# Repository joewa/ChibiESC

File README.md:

# ChibiESC

Free electric speed controller software using ChibiOS

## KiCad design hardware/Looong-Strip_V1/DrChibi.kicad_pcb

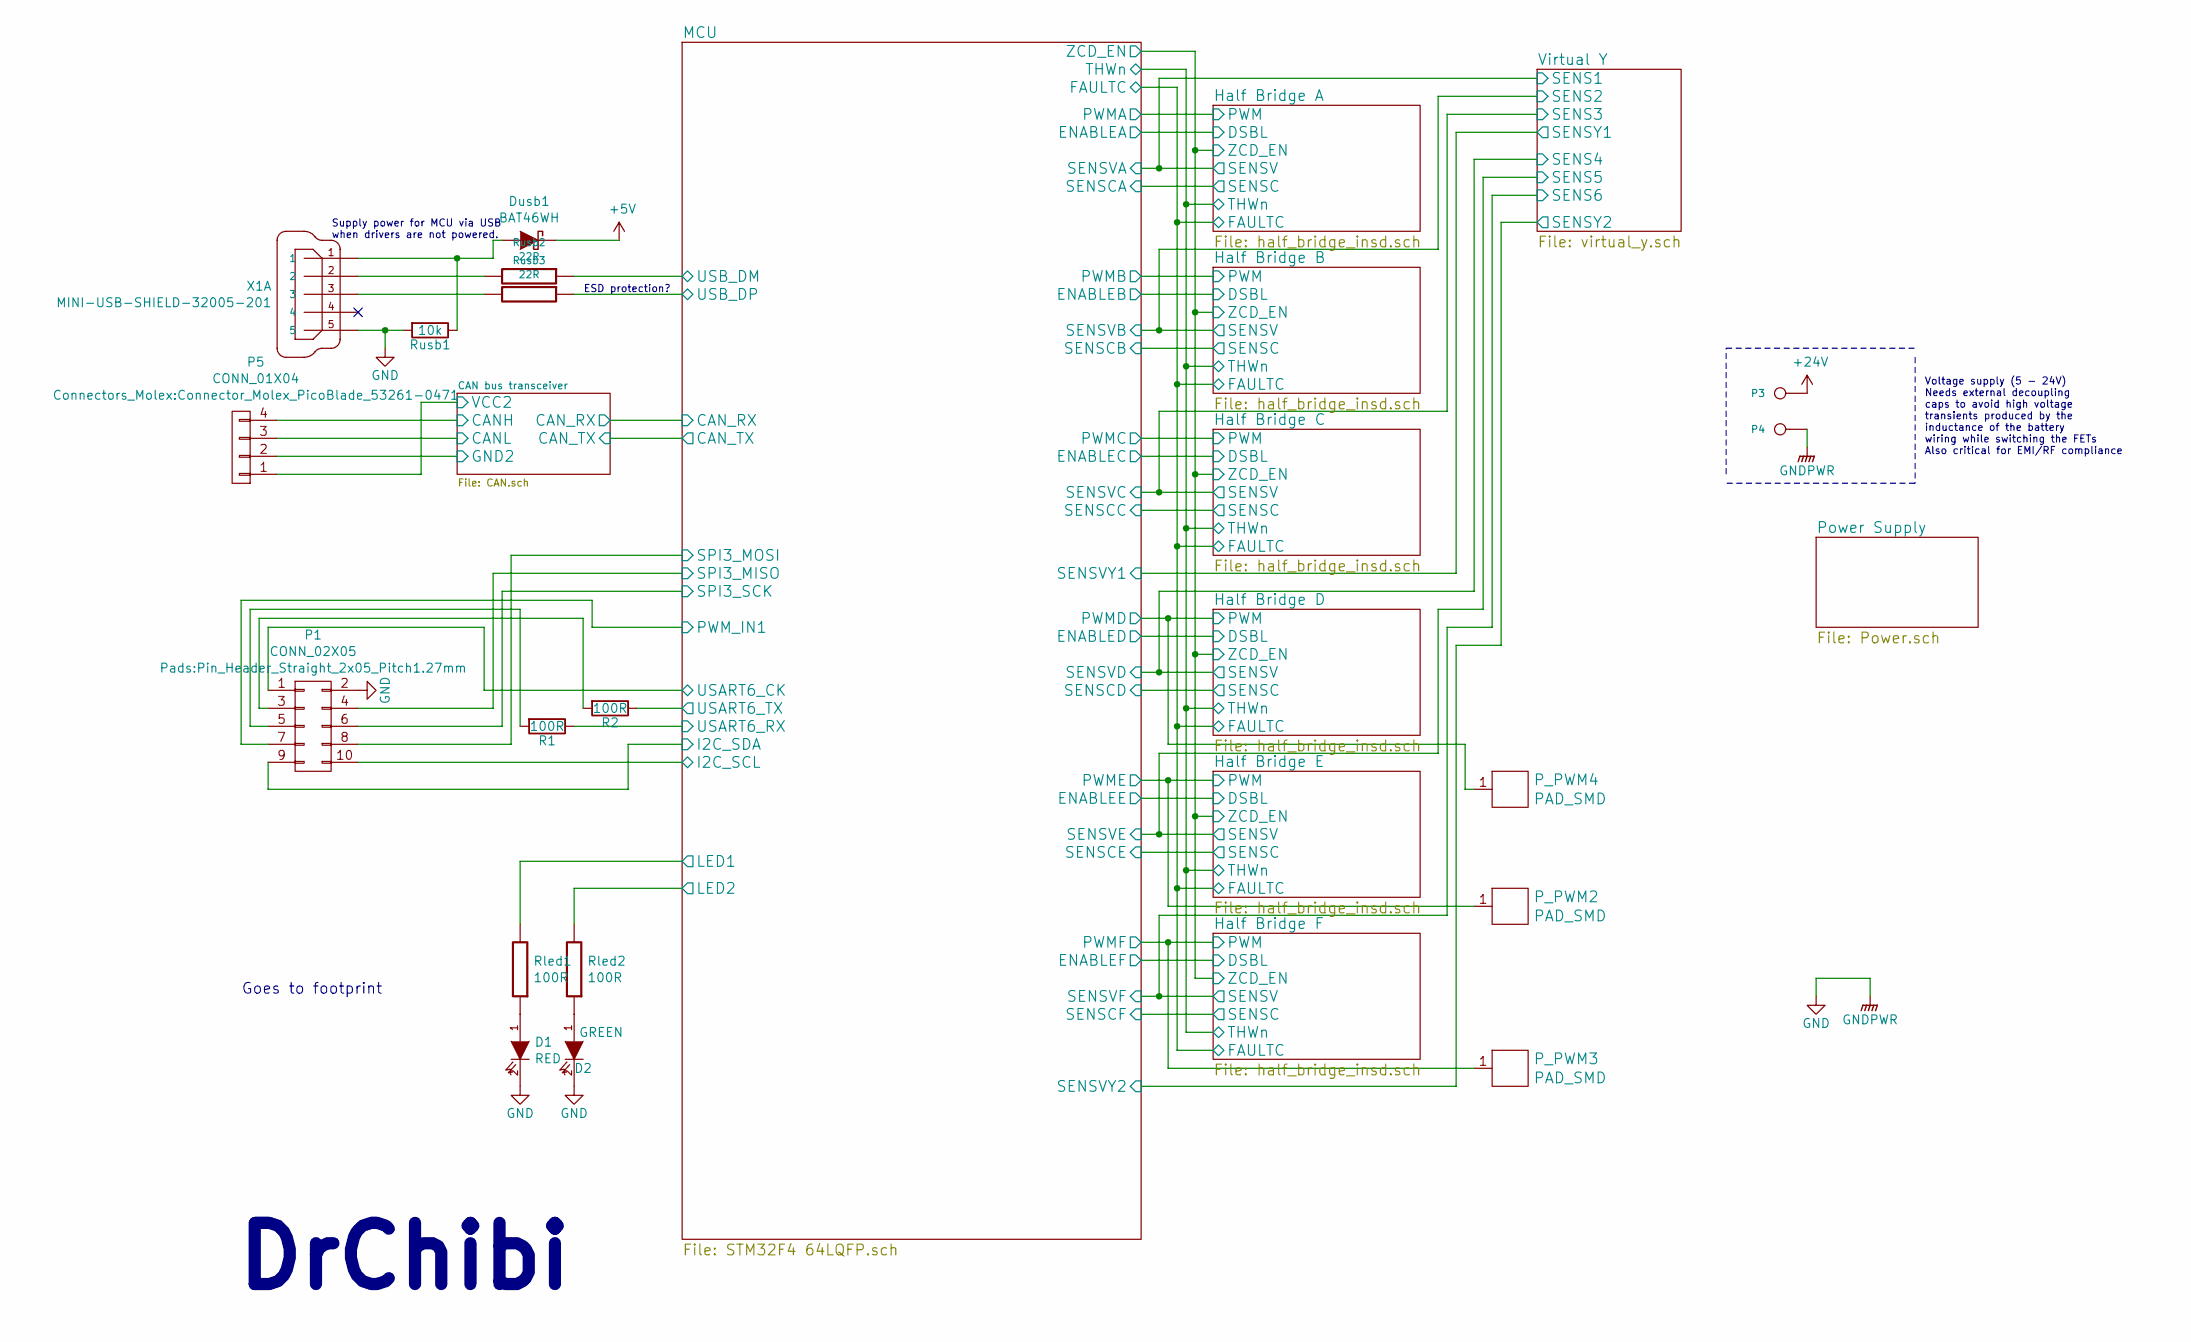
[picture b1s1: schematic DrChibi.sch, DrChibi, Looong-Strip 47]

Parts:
D1: RED; LED_0402
D2: GREEN; LED_0402
Dusb1: BAT46WH; SOD-123; Part Number BAT46WH
P1: CONN_02X05; Pin_Header_Straight_2x05_Pitch1.27mm
P3: IN+; 1PAD_3x6mm
P4: IN-; 1PAD_3.5x6mm
P5: CONN_01X04; Connector_Molex_PicoBlade_53261-0471; Part Number PicoBlade 53261-0471
P_PWM2, P_PWM3, P_PWM4: PAD_SMD; PAD_SMD_1x1
R1, R2: 100R; R_0603
Rled1, Rled2: 100R; R_0402
Rusb1: 10k; R_0402
Rusb2, Rusb3: 22R; R_0402
X1: MINI-USB-SHIELD-32005-201; mini_USB_gnd; Part Number CCMUSBB-32005-201

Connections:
+5V: Dusb1.1 (K); also elsewhere on the board
+24V: P3.1; also elsewhere on the board
/CAN bus transceiver/CANH: P5.4; also elsewhere on the board
/CAN bus transceiver/CANL: P5.3; also elsewhere on the board
/CAN bus transceiver/GND2: P5.2; also elsewhere on the board
/CAN bus transceiver/VCC2: P5.1; also elsewhere on the board
/Half Bridge D/PWM: P_PWM4.1; also elsewhere on the board
/Half Bridge E/PWM: P_PWM2.1; also elsewhere on the board
/Half Bridge F/PWM: P_PWM3.1; also elsewhere on the board
/MCU/I2C_SCL: P1.10; also elsewhere on the board
/MCU/I2C_SDA: P1.9; also elsewhere on the board
/MCU/LED1: Rled1.2; also elsewhere on the board
/MCU/LED2: Rled2.2; also elsewhere on the board
/MCU/PWM_IN1: P1.7; also elsewhere on the board
/MCU/SPI3_MISO: P1.4; also elsewhere on the board
/MCU/SPI3_MOSI: P1.8; also elsewhere on the board
/MCU/SPI3_SCK: P1.6; also elsewhere on the board
/MCU/USART6_CK: P1.1; also elsewhere on the board
/MCU/USART6_RX: R1.1; also elsewhere on the board
/MCU/USART6_TX: R2.1; also elsewhere on the board
/MCU/USB_DM: Rusb2.1; also elsewhere on the board
/MCU/USB_DP: Rusb3.1; also elsewhere on the board
GND: D1.2 (K), D2.2 (K), P1.2, P4.1, Rusb1.2, X1.5; also elsewhere on the board
unnamed: D1.1 (A), Rled1.1
unnamed: D2.1 (A), Rled2.1
unnamed: Dusb1.2 (A), Rusb1.1, X1.1
unnamed: P1.3, R2.2
unnamed: P1.5, R1.2
unnamed: Rusb2.2, X1.2
unnamed: Rusb3.2, X1.3

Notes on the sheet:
Supply power for MCU via USB when drivers are not powered.
ESD protection?
DrChibi
Voltage supply (5 - 24V) Needs external decoupling caps to avoid high voltage transients produced by the inductance of the battery wiring while switching the FETs Also critical for EMI/RF compliance
Goes to footprint

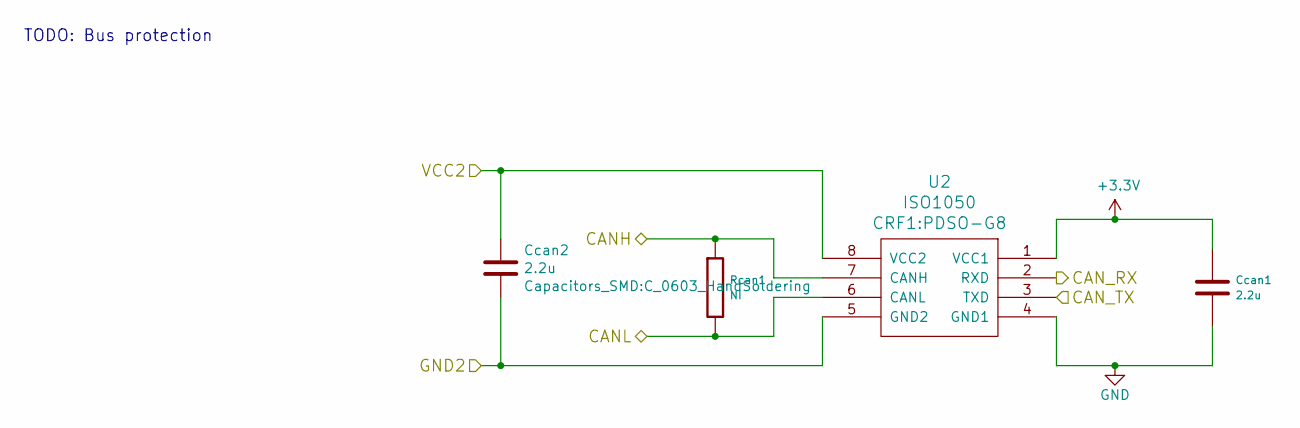
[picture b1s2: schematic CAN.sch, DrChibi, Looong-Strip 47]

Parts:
Ccan1: 2.2u; C_0603
Ccan2: 2.2u; C_0603_HandSoldering
Rcan1: NI; R_0603_HandSoldering
U2: ISO1050; PDSO-G8

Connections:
+3V3: Ccan1.1, U2.1 (VCC1); also elsewhere on the board
/CAN bus transceiver/CANH: Rcan1.1, U2.7 (CANH); also elsewhere on the board
/CAN bus transceiver/CANL: Rcan1.2, U2.6 (CANL); also elsewhere on the board
/CAN bus transceiver/CAN_RX: U2.2 (RXD); also elsewhere on the board
/CAN bus transceiver/CAN_TX: U2.3 (TXD); also elsewhere on the board
/CAN bus transceiver/GND2: Ccan2.2, U2.5 (GND2); also elsewhere on the board
/CAN bus transceiver/VCC2: Ccan2.1, U2.8 (VCC2); also elsewhere on the board
GND: Ccan1.2, U2.4 (GND1); also elsewhere on the board

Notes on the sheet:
TODO: Bus protection

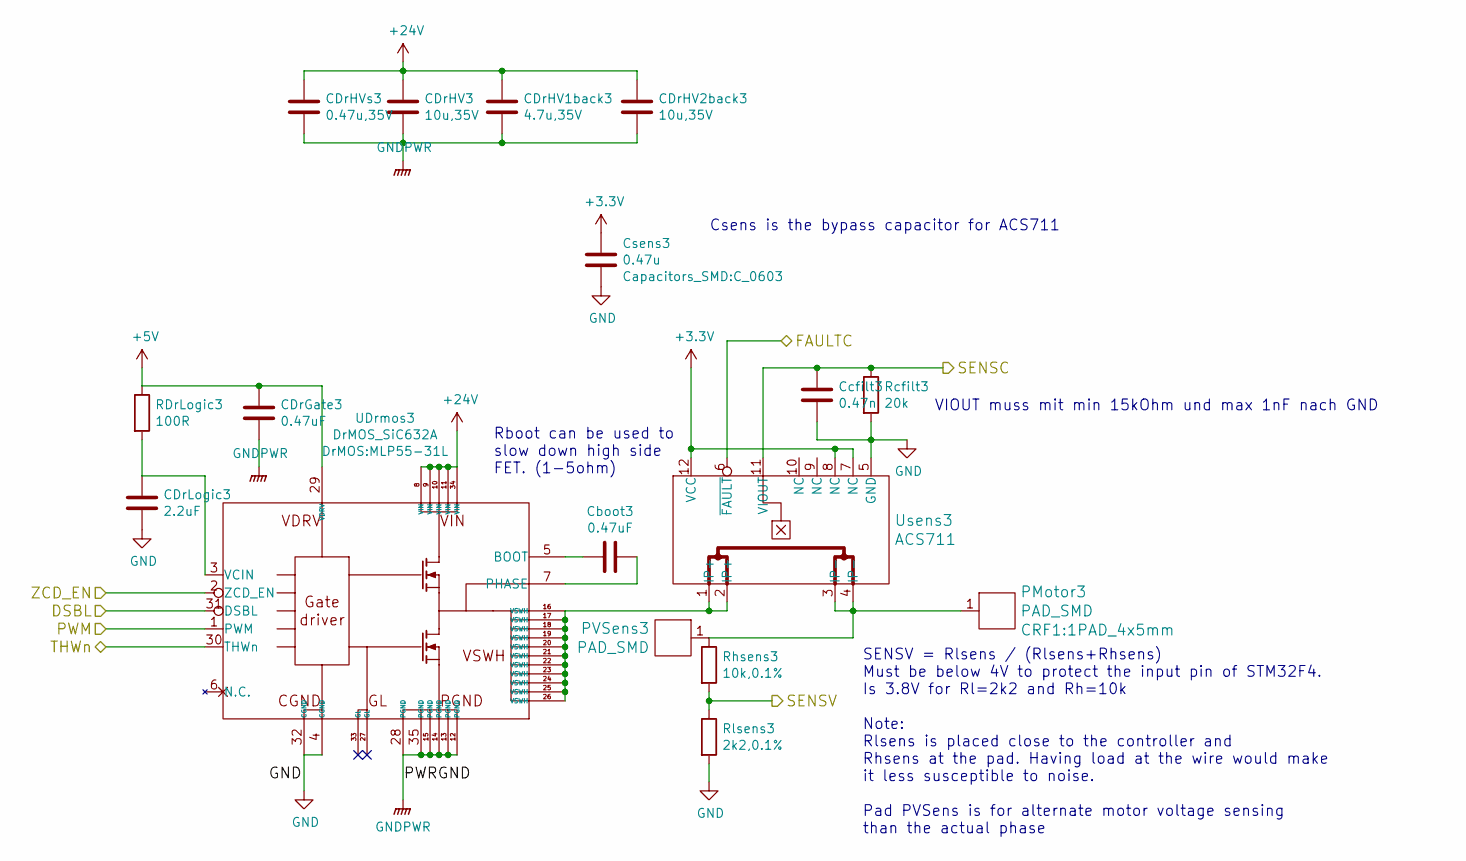
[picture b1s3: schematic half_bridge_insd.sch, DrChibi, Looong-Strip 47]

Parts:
CDrGate1: 0.47uF; C_0603_HandSoldering
CDrHV1: 10u,35V; C_1206
CDrHV1back1: 4.7u,35V; C_1206
CDrHV2back1: 10u,35V; C_1206_HandSoldering
CDrHVs1: 0.47u,35V; C_0603
CDrLogic1: 2.2uF; C_0603; Part Number C0603C225K8RACTU
Cboot1: 0.47uF; C_0603_HandSoldering
Ccfilt1: 0.47n; C_0402
Csens1: 0.47u; C_0603
PMotor1: PAD_SMD; 1PAD_4x5mm
PVSens1: PAD_SMD; PAD_SMD_1x1
RDrLogic1: 100R; R_0603
Rcfilt1: 20k; R_0402
Rhsens1: 10k,0.1%; C_0603_HandSoldering
Rlsens1: 2k2,0.1%; R_0402
UDrmos1: DrMOS_SiC632A; MLP55-31L; Part Number SiC632ACD-T1-GE3
Usens1: ACS711; QFN-12-1EX_3x3mm_Pitch0.5mm; Part Number ACS711KEXLT-31AB-T

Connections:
+3V3: Csens1.1, Usens1.7 (NC), Usens1.8 (NC), Usens1.12 (VCC); also elsewhere on the board
+5V: CDrGate1.1, RDrLogic1.1, UDrmos1.29 (VDRV); also elsewhere on the board
+24V: CDrHV1.1, CDrHV1back1.1, CDrHV2back1.1, CDrHVs1.1, UDrmos1.8 (VIN), UDrmos1.9 (VIN), UDrmos1.10 (VIN), UDrmos1.11 (VIN), UDrmos1.34 (VIN); also elsewhere on the board
/Half Bridge A/DSBL: UDrmos1.31 (DSBL); also elsewhere on the board
/Half Bridge A/FAULTC: Usens1.6 (~FAULT); also elsewhere on the board
/Half Bridge A/PWM: UDrmos1.1 (PWM); also elsewhere on the board
/Half Bridge A/SENSC: Ccfilt1.1, Rcfilt1.1, Usens1.11 (VIOUT); also elsewhere on the board
/Half Bridge A/THWn: UDrmos1.30 (THWn); also elsewhere on the board
/Half Bridge A/ZCD_EN: UDrmos1.2 (ZCD_EN); also elsewhere on the board
/Virtual Y/SENS1: Rhsens1.2, Rlsens1.1; also elsewhere on the board
GND: CDrGate1.2, CDrHV1.2, CDrHV1back1.2, CDrHV2back1.2, CDrHVs1.2, CDrLogic1.2, Ccfilt1.2, Csens1.2, Rcfilt1.2, Rlsens1.2, UDrmos1.4 (CGND), UDrmos1.12 (PGND), UDrmos1.13 (PGND), UDrmos1.14 (PGND), UDrmos1.15 (PGND), UDrmos1.28 (PGND), UDrmos1.32 (CGND), UDrmos1.35 (PGND), Usens1.5 (GND); also elsewhere on the board
unnamed: CDrLogic1.1, RDrLogic1.2, UDrmos1.3 (VCIN)
unnamed: Cboot1.1, UDrmos1.7 (PHASE)
unnamed: Cboot1.2, UDrmos1.5 (BOOT)
unnamed: PMotor1.1, PVSens1.1, Rhsens1.1, Usens1.3 (IP-), Usens1.4 (IP-)
unnamed: UDrmos1.16 (VSWH), UDrmos1.17 (VSWH), UDrmos1.18 (VSWH), UDrmos1.19 (VSWH), UDrmos1.20 (VSWH), UDrmos1.21 (VSWH), UDrmos1.22 (VSWH), UDrmos1.23 (VSWH), UDrmos1.24 (VSWH), UDrmos1.25 (VSWH), UDrmos1.26 (VSWH), Usens1.1 (IP+), Usens1.2 (IP+)

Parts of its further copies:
C20, C21, C22, C23: 0.47uF; C_0603_HandSoldering
CDrGate2, CDrGate3, CDrGate4, CDrGate5, CDrGate6: 0.47uF; C_0603_HandSoldering
CDrHV1back2, CDrHV1back3, CDrHV1back4, CDrHV1back5, CDrHV1back6: 4.7u,35V; C_1206
CDrHV2, CDrHV3, CDrHV4, CDrHV5, CDrHV6: 10u,35V; C_1206
CDrHV2back2, CDrHV2back3, CDrHV2back4, CDrHV2back5, CDrHV2back6: 10u,35V; C_1206_HandSoldering
CDrHVs2, CDrHVs3, CDrHVs4, CDrHVs5, CDrHVs6: 0.47u,35V; C_0603
CDrLogic2, CDrLogic3, CDrLogic4, CDrLogic5, CDrLogic6: 2.2uF; C_0603; Part Number C0603C225K8RACTU
Cboot2, Cboot3, Cboot4, Cboot5, Cboot6: 0.47uF; C_0603_HandSoldering
Ccfilt2, Ccfilt3, Ccfilt4, Ccfilt5, Ccfilt6: 0.47n; C_0402
Csens2, Csens3, Csens4, Csens5, Csens6: 0.47u; C_0603
PMotor2, PMotor3, PMotor4, PMotor5, PMotor6: PAD_SMD; 1PAD_4x5mm
PVSens2, PVSens3, PVSens4, PVSens5, PVSens6: PAD_SMD; PAD_SMD_1x1
RDrLogic2, RDrLogic3, RDrLogic4, RDrLogic5, RDrLogic6: 100R; R_0603
Rcfilt2, Rcfilt3, Rcfilt4, Rcfilt5, Rcfilt6: 20k; R_0402
Rhsens2, Rhsens3, Rhsens4, Rhsens5, Rhsens6: 10k,0.1%; C_0603_HandSoldering
Rlsens2, Rlsens3, Rlsens4, Rlsens5, Rlsens6: 2k2,0.1%; R_0402
UDrmos2, UDrmos3, UDrmos4, UDrmos5, UDrmos6: DrMOS_SiC632A; MLP55-31L; Part Number SiC632ACD-T1-GE3
Usens2, Usens3, Usens4, Usens5, Usens6: ACS711; QFN-12-1EX_3x3mm_Pitch0.5mm; Part Number ACS711KEXLT-31AB-T

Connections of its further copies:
+3V3: Csens2.1, Csens3.1, Csens4.1, Csens5.1, Csens6.1, Usens2.7 (NC), Usens2.8 (NC), Usens2.12 (VCC), Usens3.7 (NC), Usens3.8 (NC), Usens3.12 (VCC), Usens4.7 (NC), Usens4.8 (NC), Usens4.12 (VCC), Usens5.7 (NC), Usens5.8 (NC), Usens5.12 (VCC), Usens6.7 (NC), Usens6.8 (NC), Usens6.12 (VCC); also elsewhere on the board
+5V: CDrGate2.1, CDrGate3.1, CDrGate4.1, CDrGate5.1, CDrGate6.1, RDrLogic2.1, RDrLogic3.1, RDrLogic4.1, RDrLogic5.1, RDrLogic6.1, UDrmos2.29 (VDRV), UDrmos3.29 (VDRV), UDrmos4.29 (VDRV), UDrmos5.29 (VDRV), UDrmos6.29 (VDRV); also elsewhere on the board
+24V: CDrHV1back2.1, CDrHV1back3.1, CDrHV1back4.1, CDrHV1back5.1, CDrHV1back6.1, CDrHV2.1, CDrHV2back2.1, CDrHV2back3.1, CDrHV2back4.1, CDrHV2back5.1, CDrHV2back6.1, CDrHV3.1, CDrHV4.1, CDrHV5.1, CDrHV6.1, CDrHVs2.1, CDrHVs3.1, CDrHVs4.1, CDrHVs5.1, CDrHVs6.1, UDrmos2.8 (VIN), UDrmos2.9 (VIN), UDrmos2.10 (VIN), UDrmos2.11 (VIN), UDrmos2.34 (VIN), UDrmos3.8 (VIN), UDrmos3.9 (VIN), UDrmos3.10 (VIN), UDrmos3.11 (VIN), UDrmos3.34 (VIN), UDrmos4.8 (VIN), UDrmos4.9 (VIN), UDrmos4.10 (VIN), UDrmos4.11 (VIN), UDrmos4.34 (VIN), UDrmos5.8 (VIN), UDrmos5.9 (VIN), UDrmos5.10 (VIN), UDrmos5.11 (VIN), UDrmos5.34 (VIN), UDrmos6.8 (VIN), UDrmos6.9 (VIN), UDrmos6.10 (VIN), UDrmos6.11 (VIN), UDrmos6.34 (VIN); also elsewhere on the board
/Half Bridge A/FAULTC: Usens2.6 (~FAULT), Usens3.6 (~FAULT), Usens4.6 (~FAULT), Usens5.6 (~FAULT), Usens6.6 (~FAULT); also elsewhere on the board
/Half Bridge A/THWn: UDrmos2.30 (THWn), UDrmos3.30 (THWn), UDrmos4.30 (THWn), UDrmos5.30 (THWn), UDrmos6.30 (THWn); also elsewhere on the board
/Half Bridge A/ZCD_EN: UDrmos2.2 (ZCD_EN), UDrmos3.2 (ZCD_EN), UDrmos4.2 (ZCD_EN), UDrmos5.2 (ZCD_EN), UDrmos6.2 (ZCD_EN); also elsewhere on the board
/Half Bridge B/DSBL: UDrmos2.31 (DSBL); also elsewhere on the board
/Half Bridge B/PWM: UDrmos2.1 (PWM); also elsewhere on the board
/Half Bridge B/SENSC: Ccfilt2.1, Rcfilt2.1, Usens2.11 (VIOUT); also elsewhere on the board
/Half Bridge C/DSBL: UDrmos3.31 (DSBL); also elsewhere on the board
/Half Bridge C/PWM: UDrmos3.1 (PWM); also elsewhere on the board
/Half Bridge C/SENSC: Ccfilt3.1, Rcfilt3.1, Usens3.11 (VIOUT); also elsewhere on the board
/Half Bridge D/DSBL: UDrmos4.31 (DSBL); also elsewhere on the board
/Half Bridge D/PWM: UDrmos4.1 (PWM); also elsewhere on the board
/Half Bridge D/SENSC: Ccfilt4.1, Rcfilt4.1, Usens4.11 (VIOUT); also elsewhere on the board
/Half Bridge E/DSBL: UDrmos5.31 (DSBL); also elsewhere on the board
/Half Bridge E/PWM: UDrmos5.1 (PWM); also elsewhere on the board
/Half Bridge E/SENSC: Ccfilt5.1, Rcfilt5.1, Usens5.11 (VIOUT); also elsewhere on the board
/Half Bridge F/DSBL: UDrmos6.31 (DSBL); also elsewhere on the board
/Half Bridge F/PWM: UDrmos6.1 (PWM); also elsewhere on the board
/Half Bridge F/SENSC: Ccfilt6.1, Rcfilt6.1, Usens6.11 (VIOUT); also elsewhere on the board
/Virtual Y/SENS2: Rhsens2.2, Rlsens2.1; also elsewhere on the board
/Virtual Y/SENS3: Rhsens3.2, Rlsens3.1; also elsewhere on the board
/Virtual Y/SENS4: Rhsens4.2, Rlsens4.1; also elsewhere on the board
/Virtual Y/SENS5: Rhsens5.2, Rlsens5.1; also elsewhere on the board
/Virtual Y/SENS6: Rhsens6.2, Rlsens6.1; also elsewhere on the board
GND: CDrGate2.2, CDrGate3.2, CDrGate4.2, CDrGate5.2, CDrGate6.2, CDrHV1back2.2, CDrHV1back3.2, CDrHV1back4.2, CDrHV1back5.2, CDrHV1back6.2, CDrHV2.2, CDrHV2back2.2, CDrHV2back3.2, CDrHV2back4.2, CDrHV2back5.2, CDrHV2back6.2, CDrHV3.2, CDrHV4.2, CDrHV5.2, CDrHV6.2, CDrHVs2.2, CDrHVs3.2, CDrHVs4.2, CDrHVs5.2, CDrHVs6.2, CDrLogic2.2, CDrLogic3.2, CDrLogic4.2, CDrLogic5.2, CDrLogic6.2, Ccfilt2.2, Ccfilt3.2, Ccfilt4.2, Ccfilt5.2, Ccfilt6.2, Csens2.2, Csens3.2, Csens4.2, Csens5.2, Csens6.2, Rcfilt2.2, Rcfilt3.2, Rcfilt4.2, Rcfilt5.2, Rcfilt6.2, Rlsens2.2, Rlsens3.2, Rlsens4.2, Rlsens5.2, Rlsens6.2, UDrmos2.4 (CGND), UDrmos2.12 (PGND), UDrmos2.13 (PGND), UDrmos2.14 (PGND), UDrmos2.15 (PGND), UDrmos2.28 (PGND), UDrmos2.32 (CGND), UDrmos2.35 (PGND), UDrmos3.4 (CGND), UDrmos3.12 (PGND), UDrmos3.13 (PGND), UDrmos3.14 (PGND), UDrmos3.15 (PGND), UDrmos3.28 (PGND), UDrmos3.32 (CGND), UDrmos3.35 (PGND), UDrmos4.4 (CGND), UDrmos4.12 (PGND), UDrmos4.13 (PGND), UDrmos4.14 (PGND), UDrmos4.15 (PGND), UDrmos4.28 (PGND), UDrmos4.32 (CGND), UDrmos4.35 (PGND), UDrmos5.4 (CGND), UDrmos5.12 (PGND), UDrmos5.13 (PGND), UDrmos5.14 (PGND), UDrmos5.15 (PGND), UDrmos5.28 (PGND), UDrmos5.32 (CGND), UDrmos5.35 (PGND), UDrmos6.4 (CGND), UDrmos6.12 (PGND), UDrmos6.13 (PGND), UDrmos6.14 (PGND), UDrmos6.15 (PGND), UDrmos6.28 (PGND), UDrmos6.32 (CGND), UDrmos6.35 (PGND), Usens2.5 (GND), Usens3.5 (GND), Usens4.5 (GND), Usens5.5 (GND), Usens6.5 (GND); also elsewhere on the board
unnamed: CDrLogic2.1, RDrLogic2.2, UDrmos2.3 (VCIN)
unnamed: CDrLogic3.1, RDrLogic3.2, UDrmos3.3 (VCIN)
unnamed: CDrLogic4.1, RDrLogic4.2, UDrmos4.3 (VCIN)
unnamed: CDrLogic5.1, RDrLogic5.2, UDrmos5.3 (VCIN)
unnamed: CDrLogic6.1, RDrLogic6.2, UDrmos6.3 (VCIN)
unnamed: Cboot2.1, UDrmos2.7 (PHASE)
unnamed: Cboot2.2, UDrmos2.5 (BOOT)
unnamed: Cboot3.1, UDrmos3.7 (PHASE)
unnamed: Cboot3.2, UDrmos3.5 (BOOT)
unnamed: Cboot4.1, UDrmos4.7 (PHASE)
unnamed: Cboot4.2, UDrmos4.5 (BOOT)
unnamed: Cboot5.1, UDrmos5.7 (PHASE)
unnamed: Cboot5.2, UDrmos5.5 (BOOT)
unnamed: Cboot6.1, UDrmos6.7 (PHASE)
unnamed: Cboot6.2, UDrmos6.5 (BOOT)
unnamed: PMotor2.1, PVSens2.1, Rhsens2.1, Usens2.3 (IP-), Usens2.4 (IP-)
unnamed: PMotor3.1, PVSens3.1, Rhsens3.1, Usens3.3 (IP-), Usens3.4 (IP-)
unnamed: PMotor4.1, PVSens4.1, Rhsens4.1, Usens4.3 (IP-), Usens4.4 (IP-)
unnamed: PMotor5.1, PVSens5.1, Rhsens5.1, Usens5.3 (IP-), Usens5.4 (IP-)
unnamed: PMotor6.1, PVSens6.1, Rhsens6.1, Usens6.3 (IP-), Usens6.4 (IP-)
unnamed: UDrmos2.16 (VSWH), UDrmos2.17 (VSWH), UDrmos2.18 (VSWH), UDrmos2.19 (VSWH), UDrmos2.20 (VSWH), UDrmos2.21 (VSWH), UDrmos2.22 (VSWH), UDrmos2.23 (VSWH), UDrmos2.24 (VSWH), UDrmos2.25 (VSWH), UDrmos2.26 (VSWH), Usens2.1 (IP+), Usens2.2 (IP+)
unnamed: UDrmos3.16 (VSWH), UDrmos3.17 (VSWH), UDrmos3.18 (VSWH), UDrmos3.19 (VSWH), UDrmos3.20 (VSWH), UDrmos3.21 (VSWH), UDrmos3.22 (VSWH), UDrmos3.23 (VSWH), UDrmos3.24 (VSWH), UDrmos3.25 (VSWH), UDrmos3.26 (VSWH), Usens3.1 (IP+), Usens3.2 (IP+)
unnamed: UDrmos4.16 (VSWH), UDrmos4.17 (VSWH), UDrmos4.18 (VSWH), UDrmos4.19 (VSWH), UDrmos4.20 (VSWH), UDrmos4.21 (VSWH), UDrmos4.22 (VSWH), UDrmos4.23 (VSWH), UDrmos4.24 (VSWH), UDrmos4.25 (VSWH), UDrmos4.26 (VSWH), Usens4.1 (IP+), Usens4.2 (IP+)
unnamed: UDrmos5.16 (VSWH), UDrmos5.17 (VSWH), UDrmos5.18 (VSWH), UDrmos5.19 (VSWH), UDrmos5.20 (VSWH), UDrmos5.21 (VSWH), UDrmos5.22 (VSWH), UDrmos5.23 (VSWH), UDrmos5.24 (VSWH), UDrmos5.25 (VSWH), UDrmos5.26 (VSWH), Usens5.1 (IP+), Usens5.2 (IP+)
unnamed: UDrmos6.16 (VSWH), UDrmos6.17 (VSWH), UDrmos6.18 (VSWH), UDrmos6.19 (VSWH), UDrmos6.20 (VSWH), UDrmos6.21 (VSWH), UDrmos6.22 (VSWH), UDrmos6.23 (VSWH), UDrmos6.24 (VSWH), UDrmos6.25 (VSWH), UDrmos6.26 (VSWH), Usens6.1 (IP+), Usens6.2 (IP+)

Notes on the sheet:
VIOUT muss mit min 15kOhm und max 1nF nach GND
Rboot can be used to slow down high side FET. (1-5ohm)
SENSV = Rlsens / (Rlsens+Rhsens) Must be below 4V to protect the input pin of STM32F4. Is 3.8V for Rl=2k2 and Rh=10k Note: Rlsens is placed close to the controller and Rhsens at the pad. Having load at the wire would make it less susceptible to noise. Pad PVSens is for alternate motor voltage sensi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
Csens is the bypass capacitor for ACS711

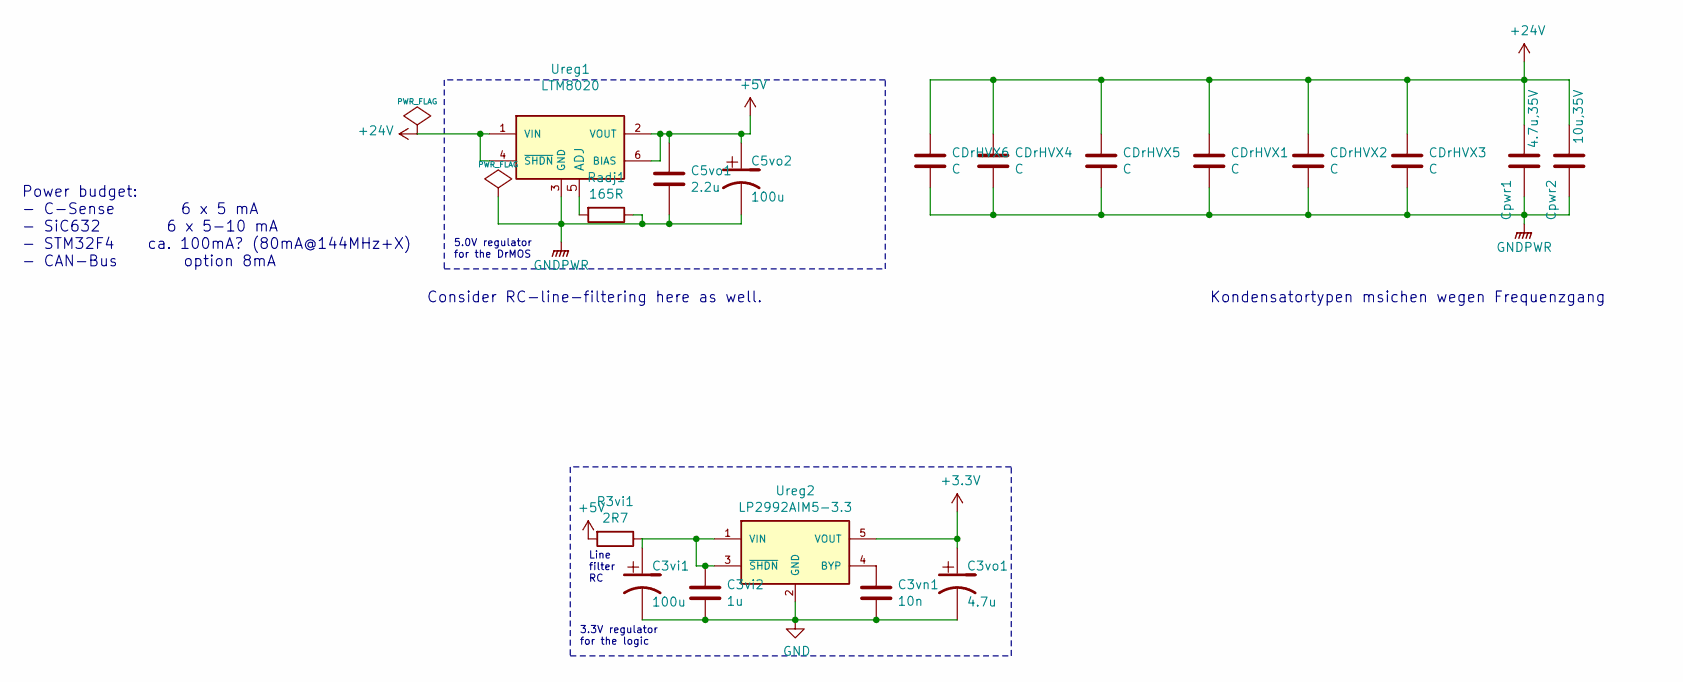
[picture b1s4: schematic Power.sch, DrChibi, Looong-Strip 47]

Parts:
C3vi1, C5vo2: 100u; C_0805
C3vi2: 1u; C_0603
C3vn1: 10n; C_0603
C3vo1: 4.7u; C_0805
C5vo1: 2.2u; C_0603
CDrHVX1, CDrHVX2, CDrHVX3, CDrHVX4, CDrHVX5, CDrHVX6: C; C_1206
Cpwr1: 4.7u,35V; C_0805
Cpwr2: 10u,35V; C_2220
R3vi1: 2R7; R_0805
Radj1: 165R; R_0402
Ureg1: LTM8020; Housings_LGA_21_6.25x6.25mm; Part Number LTM8020V
Ureg2: LP2992AIM5-3.3; SOT-23-5; Part Number LP2992AIM5-3.3/NOPB

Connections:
+3V3: C3vo1.1, Ureg2.5 (VOUT); also elsewhere on the board
+5V: C5vo1.1, C5vo2.1, R3vi1.2, Ureg1.2 (VOUT), Ureg1.6 (BIAS); also elsewhere on the board
+24V: CDrHVX1.1, CDrHVX2.1, CDrHVX3.1, CDrHVX4.1, CDrHVX5.1, CDrHVX6.1, Cpwr1.2, Cpwr2.2, Ureg1.1 (VIN), Ureg1.4 (~SHDN~); also elsewhere on the board
GND: C3vi1.2, C3vi2.2, C3vn1.2, C3vo1.2, C5vo1.2, C5vo2.2, CDrHVX1.2, CDrHVX2.2, CDrHVX3.2, CDrHVX4.2, CDrHVX5.2, CDrHVX6.2, Cpwr1.1, Cpwr2.1, Radj1.1, Ureg1.3 (GND), Ureg2.2 (GND); also elsewhere on the board
unnamed: C3vi1.1, C3vi2.1, R3vi1.1, Ureg2.1 (VIN), Ureg2.3 (~SHDN~)
unnamed: C3vn1.1, Ureg2.4 (BYP)
unnamed: Radj1.2, Ureg1.5 (ADJ)

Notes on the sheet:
5.0V regulator for the DrMOS
3.3V regulator for the logic
Kondensatortypen msichen wegen Frequenzgang
Line filter RC
Consider RC-line-filtering here as well.
Power budget: - C-Sense 6 x 5 mA - SiC632 6 x 5-10 mA - STM32F4 ca. 100mA? (80mA@144MHz+X) - CAN-Bus option 8mA

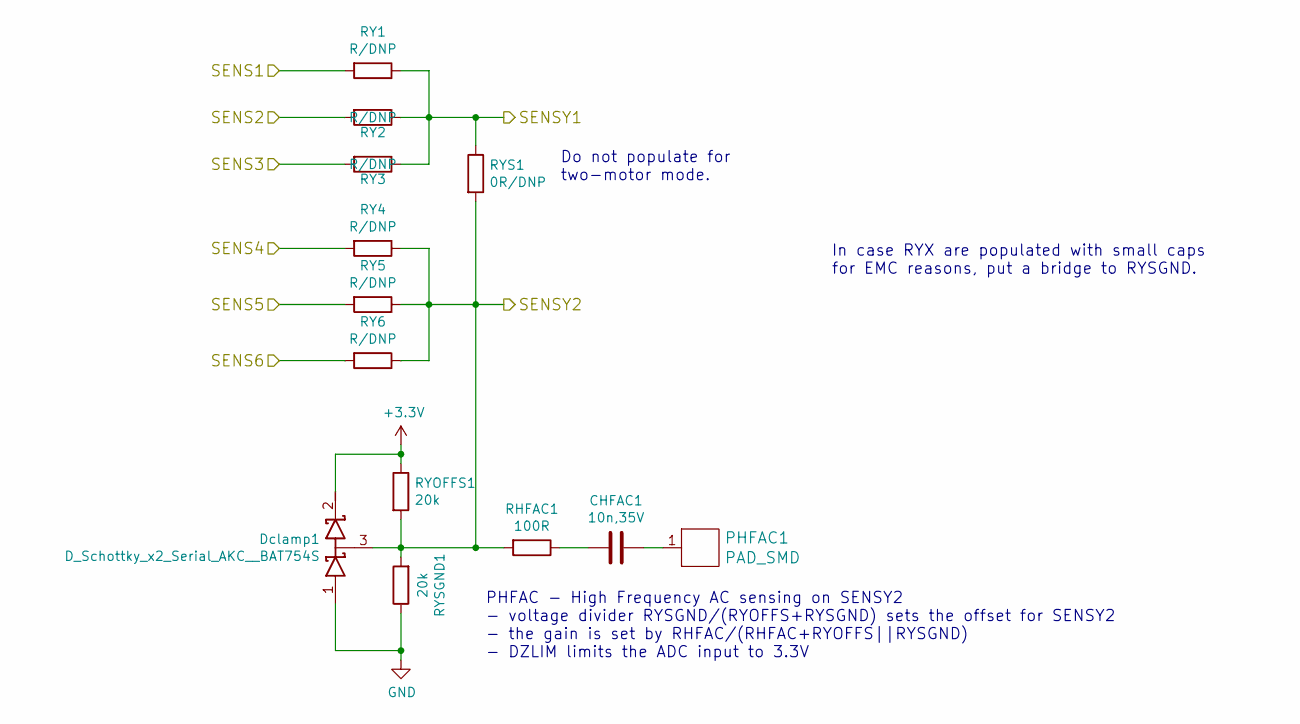
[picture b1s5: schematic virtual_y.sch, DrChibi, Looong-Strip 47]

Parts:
CHFAC1: 10n,35V; C_0603_HandSoldering
Dclamp1: D_Schottky_x2_Serial_AKC__BAT754S; SOT-23; Part Number BAT754S
PHFAC1: PAD_SMD; PAD_SMD_1.2x2.5
RHFAC1: 100R; R_0603_HandSoldering
RY1, RY2, RY3, RY4, RY5, RY6: R/DNP; R_0603_HandSoldering
RYOFFS1: 20k; R_0603_HandSoldering
RYS1: 0R/DNP; R_0603_HandSoldering
RYSGND1: 20k; R_0402

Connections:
+3V3: Dclamp1.2 (K), RYOFFS1.1; also elsewhere on the board
/MCU/SENSVY1: RY1.1, RY2.1, RY3.1, RYS1.1; also elsewhere on the board
/MCU/SENSVY2: Dclamp1.3 (common), RHFAC1.2, RY4.1, RY5.1, RY6.1, RYOFFS1.2, RYS1.2, RYSGND1.2; also elsewhere on the board
/Virtual Y/SENS1: RY1.2; also elsewhere on the board
/Virtual Y/SENS2: RY2.2; also elsewhere on the board
/Virtual Y/SENS3: RY3.2; also elsewhere on the board
/Virtual Y/SENS4: RY4.2; also elsewhere on the board
/Virtual Y/SENS5: RY5.2; also elsewhere on the board
/Virtual Y/SENS6: RY6.2; also elsewhere on the board
GND: Dclamp1.1 (A), RYSGND1.1; also elsewhere on the board
unnamed: CHFAC1.1, PHFAC1.1
unnamed: CHFAC1.2, RHFAC1.1

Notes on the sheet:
Do not populate for two-motor mode.
In case RYX are populated with small caps for EMC reasons, put a bridge to RYSGND.
PHFAC - High Frequency AC sensing on SENSY2 - voltage divider RYSGND/(RYOFFS+RYSGND) sets the offset for SENSY2 - the gain is set by RHFAC/(RHFAC+RYOFFS||RYSGND) - DZLIM limits the ADC input to 3.3V

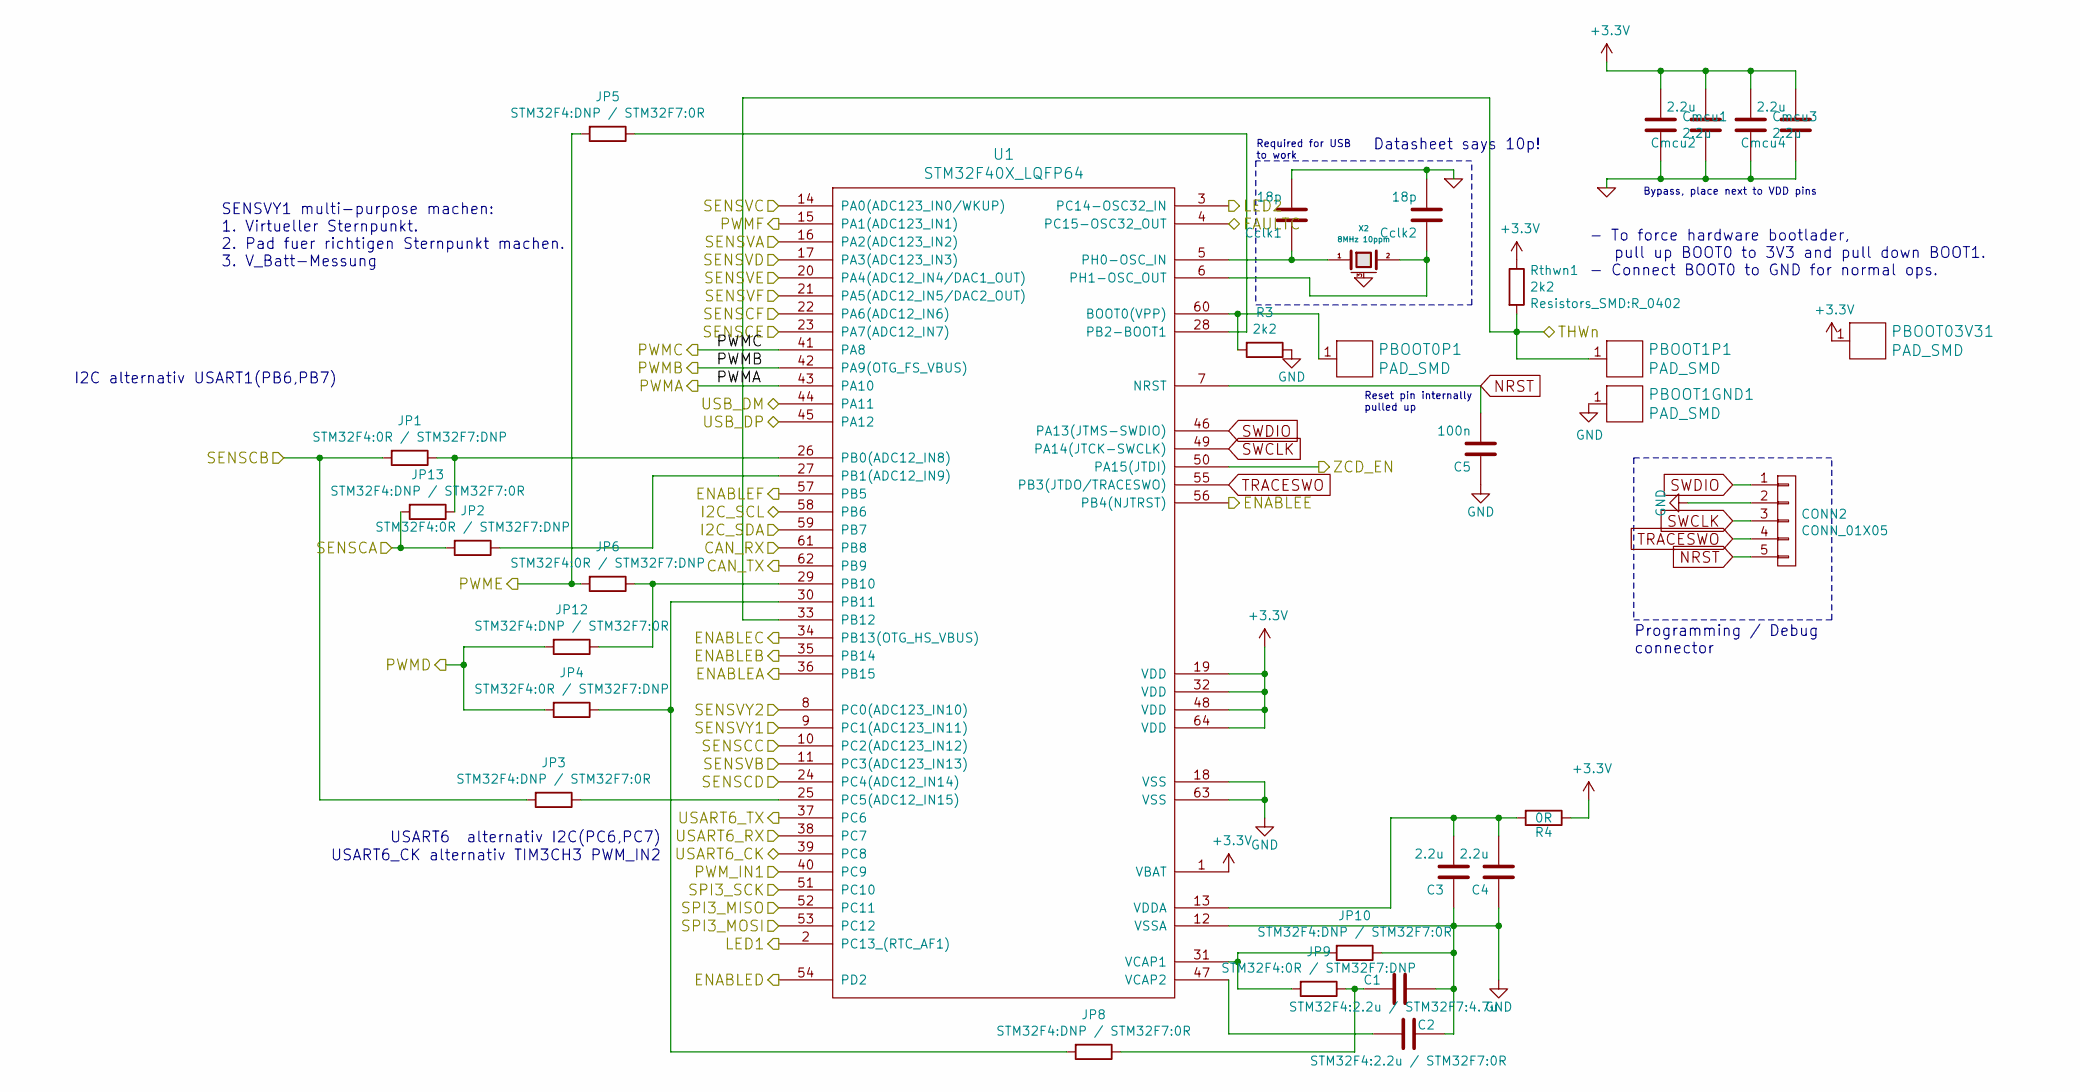
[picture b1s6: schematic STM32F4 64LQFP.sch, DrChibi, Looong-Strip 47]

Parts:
C1: STM32F4:2.2u / STM32F7:4.7u; C_0603
C2: STM32F4:2.2u / STM32F7:0R; C_0603
C3, C4: 2.2u; C_0603
C5: 100n; C_0603
CONN2: CONN_01X05; Pin_Header_Straight_1x05_Pitch1.27mm
Cclk1, Cclk2: 18p; C_0402
Cmcu1, Cmcu2, Cmcu3, Cmcu4: 2.2u; C_0603
JP1, JP2, JP4, JP6, JP9: STM32F4:0R / STM32F7:DNP; C_0402
JP3, JP5, JP8, JP10, JP12, JP13: STM32F4:DNP / STM32F7:0R; C_0402
PBOOT0P1, PBOOT1GND1, PBOOT1P1, PBOOT03V31: PAD_SMD; PAD_SMD_1x1
R3: 2k2; R_0402
R4: 0R; R_0805
Rthwn1: 2k2; R_0402
U1: STM32F40X_LQFP64; lqfp64_pad_mod; Part Number STM32F405RGTx
X2: 8MHz 10ppm; Crystal_5x3mm; Part Number ABM3B-8.0-10-1UT

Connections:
+3V3: Cmcu1.2, Cmcu2.2, Cmcu3.2, Cmcu4.2, PBOOT03V31.1, R4.1, Rthwn1.1, U1.1 (VBAT), U1.19 (VDD), U1.32 (VDD), U1.48 (VDD), U1.64 (VDD); also elsewhere on the board
/CAN bus transceiver/CAN_RX: U1.61 (PB8); also elsewhere on the board
/CAN bus transceiver/CAN_TX: U1.62 (PB9); also elsewhere on the board
/Half Bridge A/DSBL: U1.36 (PB15); also elsewhere on the board
/Half Bridge A/FAULTC: U1.4 (PC15-OSC32_OUT); also elsewhere on the board
/Half Bridge A/PWM: U1.43 (PA10); also elsewhere on the board
/Half Bridge A/SENSC: JP2.2, JP13.2; also elsewhere on the board
/Half Bridge A/THWn: PBOOT1P1.1, Rthwn1.2, U1.33 (PB12); also elsewhere on the board
/Half Bridge A/ZCD_EN: U1.50 (PA15(JTDI)); also elsewhere on the board
/Half Bridge B/DSBL: U1.35 (PB14); also elsewhere on the board
/Half Bridge B/PWM: U1.42 (PA9(OTG_FS_VBUS)); also elsewhere on the board
/Half Bridge B/SENSC: JP1.2, JP3.2; also elsewhere on the board
/Half Bridge C/DSBL: U1.34 (PB13(OTG_HS_VBUS)); also elsewhere on the board
/Half Bridge C/PWM: U1.41 (PA8); also elsewhere on the board
/Half Bridge C/SENSC: U1.10 (PC2(ADC123_IN12)); also elsewhere on the board
/Half Bridge D/DSBL: U1.54 (PD2); also elsewhere on the board
/Half Bridge D/PWM: JP4.2, JP12.2; also elsewhere on the board
/Half Bridge D/SENSC: U1.24 (PC4(ADC12_IN14)); also elsewhere on the board
/Half Bridge E/DSBL: U1.56 (PB4(NJTRST)); also elsewhere on the board
/Half Bridge E/PWM: JP5.2, JP6.2; also elsewhere on the board
/Half Bridge E/SENSC: U1.23 (PA7(ADC12_IN7)); also elsewhere on the board
/Half Bridge F/DSBL: U1.57 (PB5); also elsewhere on the board
/Half Bridge F/PWM: U1.15 (PA1(ADC123_IN1)); also elsewhere on the board
/Half Bridge F/SENSC: U1.22 (PA6(ADC12_IN6)); also elsewhere on the board
/MCU/I2C_SCL: U1.58 (PB6); also elsewhere on the board
/MCU/I2C_SDA: U1.59 (PB7); also elsewhere on the board
/MCU/LED1: U1.2 (PC13_(RTC_AF1)); also elsewhere on the board
/MCU/LED2: U1.3 (PC14-OSC32_IN); also elsewhere on the board
/MCU/PWM_IN1: U1.40 (PC9); also elsewhere on the board
/MCU/SENSVY1: U1.9 (PC1(ADC123_IN11)); also elsewhere on the board
/MCU/SENSVY2: U1.8 (PC0(ADC123_IN10)); also elsewhere on the board
/MCU/SPI3_MISO: U1.52 (PC11); also elsewhere on the board
/MCU/SPI3_MOSI: U1.53 (PC12); also elsewhere on the board
/MCU/SPI3_SCK: U1.51 (PC10); also elsewhere on the board
/MCU/USART6_CK: U1.39 (PC8); also elsewhere on the board
/MCU/USART6_RX: U1.38 (PC7); also elsewhere on the board
/MCU/USART6_TX: U1.37 (PC6); also elsewhere on the board
/MCU/USB_DM: U1.44 (PA11); also elsewhere on the board
/MCU/USB_DP: U1.45 (PA12); also elsewhere on the board
/Virtual Y/SENS1: U1.16 (PA2(ADC123_IN2)); also elsewhere on the board
/Virtual Y/SENS2: U1.11 (PC3(ADC123_IN13)); also elsewhere on the board
/Virtual Y/SENS3: U1.14 (PA0(ADC123_IN0/WKUP)); also elsewhere on the board
/Virtual Y/SENS4: U1.17 (PA3(ADC123_IN3)); also elsewhere on the board
/Virtual Y/SENS5: U1.20 (PA4(ADC12_IN4/DAC1_OUT)); also elsewhere on the board
/Virtual Y/SENS6: U1.21 (PA5(ADC12_IN5/DAC2_OUT)); also elsewhere on the board
GND: C1.2, C2.2, C3.1, C4.1, C5.1, CONN2.2, Cclk1.2, Cclk2.2, Cmcu1.1, Cmcu2.1, Cmcu3.1, Cmcu4.1, JP10.1, PBOOT1GND1.1, R3.1, U1.12 (VSSA), U1.18 (VSS), U1.63 (VSS), X2.3 (case); also elsewhere on the board
NRST: C5.2, CONN2.5, U1.7 (NRST)
unnamed: C1.1, JP8.1, JP9.1
unnamed: C2.1, U1.47 (VCAP2)
unnamed: C3.2, C4.2, R4.2, U1.13 (VDDA)
unnamed: Cclk1.1, U1.5 (PH0-OSC_IN), X2.1
unnamed: Cclk2.1, U1.6 (PH1-OSC_OUT), X2.2
unnamed: JP1.1, JP13.1, U1.26 (PB0(ADC12_IN8))
unnamed: JP2.1, U1.27 (PB1(ADC12_IN9))
unnamed: JP3.1, U1.25 (PC5(ADC12_IN15))
unnamed: JP4.1, JP8.2, U1.30 (PB11)
unnamed: JP5.1, U1.28 (PB2-BOOT1)
unnamed: JP9.2, JP10.2, U1.31 (VCAP1)
unnamed: JP6.1, JP12.1, U1.29 (PB10)
unnamed: PBOOT0P1.1, R3.2, U1.60 (BOOT0(VPP))
SWCLK: CONN2.3, U1.49 (PA14(JTCK-SWCLK))
SWDIO: CONN2.1, U1.46 (PA13(JTMS-SWDIO))
TRACESWO: CONN2.4, U1.55 (PB3(JTDO/TRACESWO))

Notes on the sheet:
Programming / Debug connector
Reset pin internally pulled up
Required for USB to work
Bypass, place next to VDD pins
SENSVY1 multi-purpose machen: 1. Virtueller Sternpunkt. 2. Pad fuer richtigen Sternpunkt machen. 3. V_Batt-Messung
I2C alternativ USART1(PB6,PB7)
USART6 alternativ I2C(PC6,PC7)
USART6_CK alternativ TIM3CH3 PWM_IN2
Datasheet says 10p!
- To force hardware bootlader, pull up BOOT0 to 3V3 and pull down BOOT1. - Connect BOOT0 to GND for normal ops.

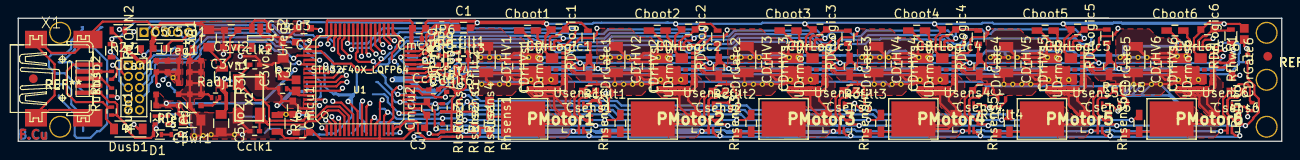
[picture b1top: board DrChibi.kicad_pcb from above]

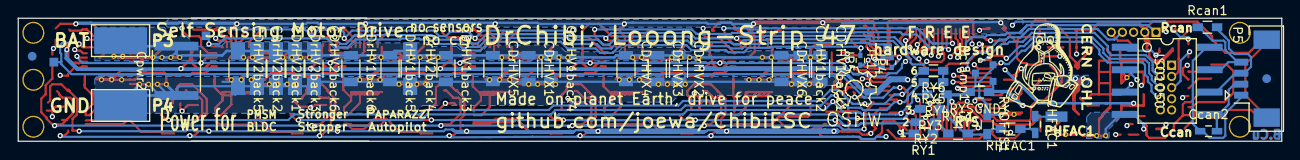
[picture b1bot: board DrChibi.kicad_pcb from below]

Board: 4 copper layers, 143.5 x 14.0 mm, 188 parts (45 on the bottom side), 111 nets.

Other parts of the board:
REFSYMOSHW: Symbol_OSHW-Logo_SilkScreen

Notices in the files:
hardware/Looong-Strip_V0/DrChibi.sch:
CC-BY-SA 4.0
hardware/Looong-Strip_V1/DrChibi.kicad_pcb:
CERN OHL
